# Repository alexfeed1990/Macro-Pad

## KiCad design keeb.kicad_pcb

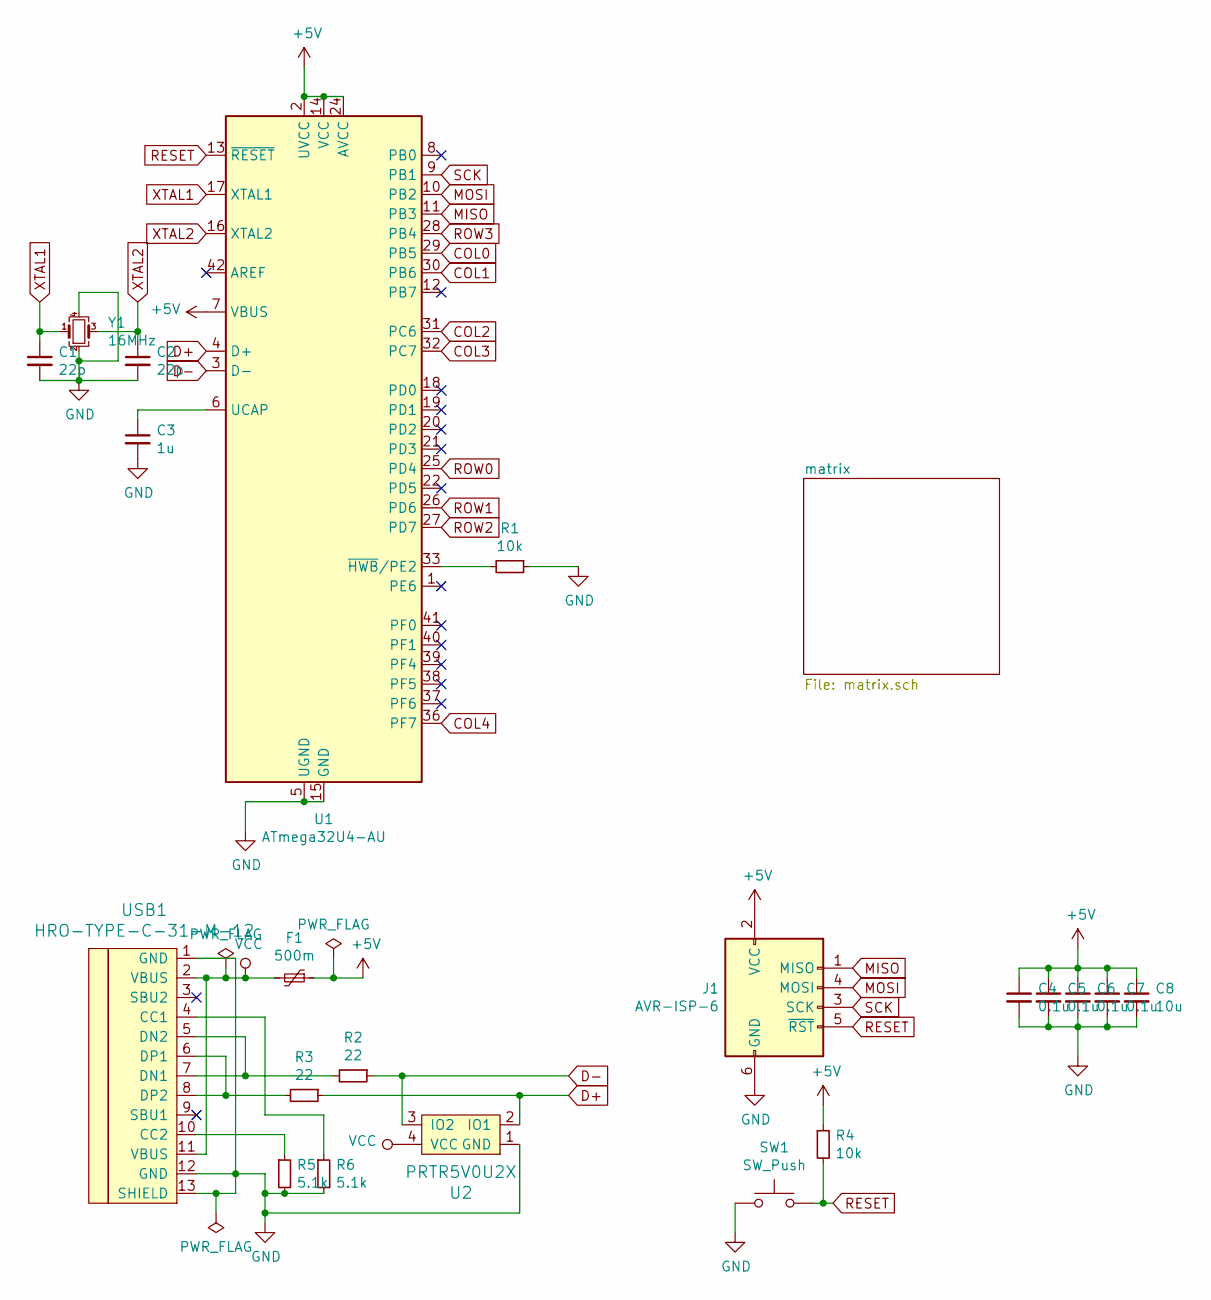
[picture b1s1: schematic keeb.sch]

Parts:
C1, C2: 22p; C_0805_2012Metric_Pad1.15x1.40mm_HandSolder
C3: 1u; C_0805_2012Metric_Pad1.15x1.40mm_HandSolder
C4, C5, C6, C7: 0.1u; C_0805_2012Metric_Pad1.15x1.40mm_HandSolder
C8: 10u; C_0805_2012Metric_Pad1.15x1.40mm_HandSolder
F1: 500m; Fuse_0805_2012Metric_Pad1.15x1.40mm_HandSolder
J1: AVR-ISP-6; Reset_Pretty-Mask
R1, R4: 10k; R_0805_2012Metric_Pad1.15x1.40mm_HandSolder
R2, R3: 22; R_0805_2012Metric_Pad1.15x1.40mm_HandSolder
R5, R6: 5.1k; R_0805_2012Metric_Pad1.15x1.40mm_HandSolder
SW1: SW_Push; SW_SPST_SKQG_WithStem
U1: ATmega32U4-AU; TQFP-44_10x10mm_P0.8mm
U2: PRTR5V0U2X; SOT143B
USB1: HRO-TYPE-C-31-M-12; HRO-TYPE-C-31-M-12-HandSoldering
Y1: 16MHz; Crystal_SMD_3225-4Pin_3.2x2.5mm_HandSoldering

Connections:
+5V: C4.1, C5.1, C6.1, C7.1, C8.1, F1.1, J1.2 (VCC), R4.1, U1.2 (UVCC), U1.7 (VBUS), U1.14 (VCC), U1.24 (AVCC), U1.34 (VCC), U1.44 (AVCC)
COL0: U1.29 (PB5); also elsewhere on the board
COL1: U1.30 (PB6); also elsewhere on the board
COL2: U1.31 (PC6); also elsewhere on the board
COL3: U1.32 (PC7); also elsewhere on the board
COL4: U1.36 (PF7); also elsewhere on the board
D+: R3.1, U1.4 (D+), U2.2 (IO1)
D-: R2.1, U1.3 (D-), U2.3 (IO2)
GND: C1.2, C2.2, C3.2, C4.2, C5.2, C6.2, C7.2, C8.2, J1.6 (GND), R1.1, R5.2, R6.2, SW1.1, U1.5 (UGND), U1.15 (GND), U1.23 (GND), U1.35 (GND), U1.43 (GND), U2.1 (GND), USB1.1 (GND), USB1.12 (GND), USB1.13 (SHIELD), Y1.2, Y1.4
MISO: J1.1 (MISO), U1.11 (PB3)
MOSI: J1.4 (MOSI), U1.10 (PB2)
unnamed: C3.1, U1.6 (UCAP)
unnamed: R1.2, U1.33 (~HWB~/PE2)
unnamed: R2.2, USB1.5 (DN2), USB1.7 (DN1)
unnamed: R3.2, USB1.6 (DP1), USB1.8 (DP2)
unnamed: R5.1, USB1.10 (CC2)
unnamed: R6.1, USB1.4 (CC1)
RESET: J1.5 (~RST), R4.2, SW1.2, U1.13 (~RESET)
ROW0: U1.25 (PD4); also elsewhere on the board
ROW1: U1.26 (PD6); also elsewhere on the board
ROW2: U1.27 (PD7); also elsewhere on the board
ROW3: U1.28 (PB4); also elsewhere on the board
SCK: J1.3 (SCK), U1.9 (PB1)
VCC: F1.2, U2.4 (VCC), USB1.2 (VBUS), USB1.11 (VBUS)
XTAL1: C1.1, U1.17 (XTAL1), Y1.1
XTAL2: C2.1, U1.16 (XTAL2), Y1.3

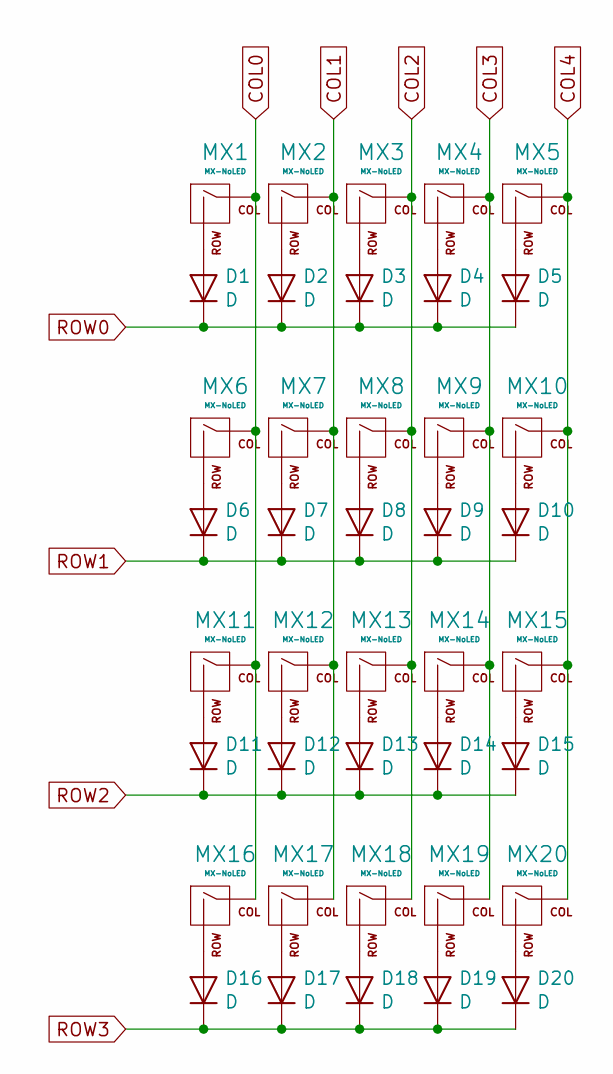
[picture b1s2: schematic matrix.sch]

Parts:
D1, D2, D3, D4, D5, D6, D7, D8, D9, D10, D11, D12, D13, D14, D15, D16, D17, D18, D19, D20: D; D_SOD-123
MX1, MX2, MX3, MX4, MX5, MX6, MX7, MX8, MX9, MX10, MX11, MX12, MX13, MX14, MX15, MX16, MX17, MX18, MX19, MX20: MX-NoLED; MXOnly-1U-Hotswap

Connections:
COL0: MX1.1 (COL), MX6.1 (COL), MX11.1 (COL), MX16.1 (COL); also elsewhere on the board
COL1: MX2.1 (COL), MX7.1 (COL), MX12.1 (COL), MX17.1 (COL); also elsewhere on the board
COL2: MX3.1 (COL), MX8.1 (COL), MX13.1 (COL), MX18.1 (COL); also elsewhere on the board
COL3: MX4.1 (COL), MX9.1 (COL), MX14.1 (COL), MX19.1 (COL); also elsewhere on the board
COL4: MX5.1 (COL), MX10.1 (COL), MX15.1 (COL), MX20.1 (COL); also elsewhere on the board
unnamed: D1.2 (A), MX1.2 (ROW)
unnamed: D2.2 (A), MX2.2 (ROW)
unnamed: D3.2 (A), MX3.2 (ROW)
unnamed: D4.2 (A), MX4.2 (ROW)
unnamed: D5.2 (A), MX5.2 (ROW)
unnamed: D6.2 (A), MX6.2 (ROW)
unnamed: D7.2 (A), MX7.2 (ROW)
unnamed: D8.2 (A), MX8.2 (ROW)
unnamed: D9.2 (A), MX9.2 (ROW)
unnamed: D10.2 (A), MX10.2 (ROW)
unnamed: D11.2 (A), MX11.2 (ROW)
unnamed: D12.2 (A), MX12.2 (ROW)
unnamed: D13.2 (A), MX13.2 (ROW)
unnamed: D14.2 (A), MX14.2 (ROW)
unnamed: D15.2 (A), MX15.2 (ROW)
unnamed: D16.2 (A), MX16.2 (ROW)
unnamed: D17.2 (A), MX17.2 (ROW)
unnamed: D18.2 (A), MX18.2 (ROW)
unnamed: D19.2 (A), MX19.2 (ROW)
unnamed: D20.2 (A), MX20.2 (ROW)
ROW0: D1.1 (K), D2.1 (K), D3.1 (K), D4.1 (K), D5.1 (K); also elsewhere on the board
ROW1: D6.1 (K), D7.1 (K), D8.1 (K), D9.1 (K), D10.1 (K); also elsewhere on the board
ROW2: D11.1 (K), D12.1 (K), D13.1 (K), D14.1 (K), D15.1 (K); also elsewhere on the board
ROW3: D16.1 (K), D17.1 (K), D18.1 (K), D19.1 (K), D20.1 (K); also elsewhere on the board

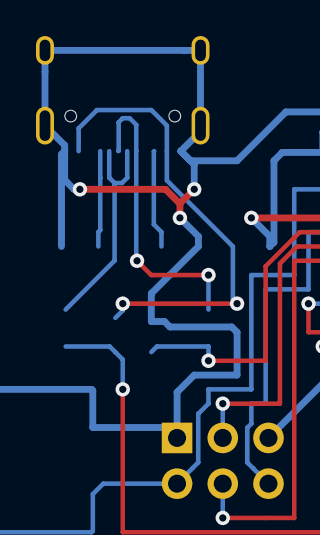
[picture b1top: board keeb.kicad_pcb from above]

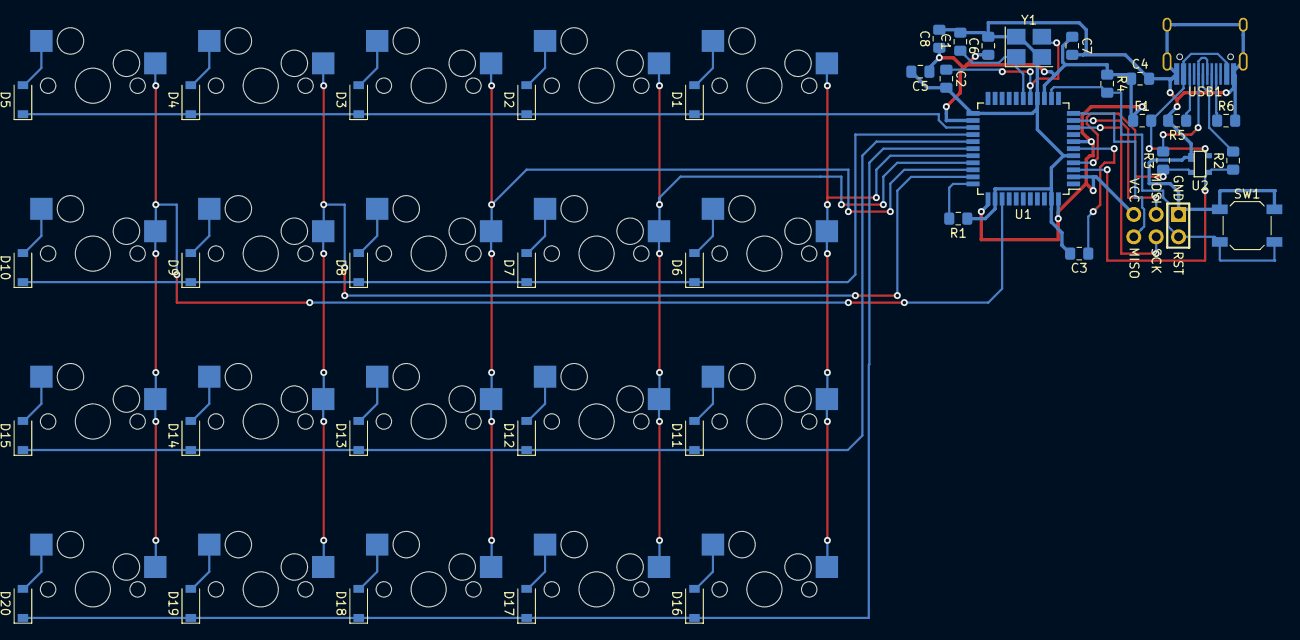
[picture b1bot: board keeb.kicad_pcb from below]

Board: 2 copper layers, 61 parts (41 on the bottom side), 46 nets.

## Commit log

2023-03-06 Add submodules and project
2023-03-06 type-c submodule
2023-03-06 Schematic & Netlist
2023-03-06 pcb layout
2023-03-06 really bad traces but atleast i hope it works
    doesn't connect key matrix to the mcu
2023-03-06 terribly connected key matrix
2023-03-06 add watermark if you just wanna copy me without knowing anything
2023-03-06 Add Gerbers & Drill files
2023-03-06 gerber zip (really unecessary)
2023-03-06 uh i think i fucked it up because i opened it in kicad 7 oops
2023-03-07 fucky wucky shit
